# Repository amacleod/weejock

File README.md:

weejock
=======

Wee Jock is a 4x5 wireless keypad with smaller than normal key
spacing.  The name "Wee Jock" is a reference to Terry Pratchett's
[The Wee Free Men][weefreemen], and is meant to convey that this
keypad is more closely spaced than normal MX spacing.

The current design places the switches in a 17mm square grid, meaning
that only small square keycaps will work. ChosFox's [ChocFox][chocfox]
line of keycaps are approximately 16.5mm square, so they ought to work
fine. MBK keycaps are rectangular and will likely interfere with each
other horizontally.

Bill of Materials
-----------------

In addition to the Gerber file in [WeeJock-0-0-3-GERBER.zip](gerber/WeeJock-0-0-3-GERBER.zip), you will need:
 - 1 Seeed Studio XIAO BLE - [XIAO BLE nRF52840][xiaoble]
   - headers -OR- sockets and pins -OR- solder paste (see below)
 - 1 power switch - [PCM12][pcm12], [CUS-12TB][cus12tb], or equivalent
 - 1 reset button - [B3U-1000P][b3u1000p] or equivalent
 - 1 through-hole, right angle JST-PH-2 jack - [S2B-PH-K-S][s2bphks]
 - 1 3.7V LiPoly battery with a JST connector
 - 20 Kailh Choc v1 key switches (PG1350)
 - 20 diodes with a SOD123 footprint - [1N4148W][diode1n4148w] or equivalent
 - 20 keycaps no larger than 16.5mm by 16.5mm (for example, ChocFox CFX)

In principle, the power switch and JST connector are optional, but
highly recommended for battery operation. If you intend to always use
the keypad connected by USB, you could omit the battery entirely.

> [!WARNING]
> **Polarity Check**: Wee Jock revisions 1, 2, and 3 have the JST-PH
> jack connected to match "Adafruit-style" battery connectors: the
> positive (red) wire should be on the left when viewed from above.
>
> Not all batteries' connectors have the same polarity, so check
> carefully before plugging one in!

If you are hand-soldering, you will need headers for the controller,
as well as pogo pins for the RST and BAT+ pins.
 - 2 seven-pin headers - [PH1-07-UA][ph107ua] (or you can cut longer headers down to size)
   - alternatively you can use sockets such as the [Preci-Dip 310][sockets] series
   - and straight pins such as [Mill-Max 3320][straightpins]
 - 2 spring pins of a height to match the headers - [Mill-Max 0906][pogo0906]

If you intend to surface mount the controller, you will need a way to
handle the RST and BAT+ pads on the back, such as solder paste and a
rework station (or at least a hotplate).

TODO:
 - find a nice way to print a 2D color render of the PCB for inclusion in this README

[weefreemen]: https://en.wikipedia.org/wiki/The_Wee_Free_Men "The Wee Free Men"
[chocfox]: https://chosfox.com/collections/low-profile-keycaps/products/chocfox-bow?variant=43632218767554
[xiaoble]: https://www.seeedstudio.com/Seeed-XIAO-BLE-nRF52840-p-5201.html
[pcm12]: https://www.digikey.com/en/products/detail/c-k/PCM12SMTR/1640112
[cus12tb]: https://www.digikey.com/en/products/detail/nidec-components-corporation/CUS-12TB/1124222
[b3u1000p]: https://www.digikey.com/en/products/detail/omron-electronics-inc-emc-div/B3U-1000P/1534338
[s2bphks]: https://www.digikey.com/en/products/detail/jst-sales-america-inc./S2B-PH-K-S/926626
[diode1n4148w]: https://www.digikey.com/en/products/detail/smc-diode-solutions/1N4148W/6022450
[ph107ua]: https://www.digikey.com/en/products/detail/adam-tech/PH1-07-UA/9830505
[sockets]: https://www.digikey.com/en/products/detail/preci-dip/310-87-115-41-001101/3757353
[straightpins]: https://www.digikey.com/en/products/detail/mill-max-manufacturing-corp/3320-0-00-15-00-00-03-0/4147392
[pogo0906]: https://www.digikey.com/en/products/detail/mill-max-manufacturing-corp/0906-2-15-20-75-14-11-0/1147050

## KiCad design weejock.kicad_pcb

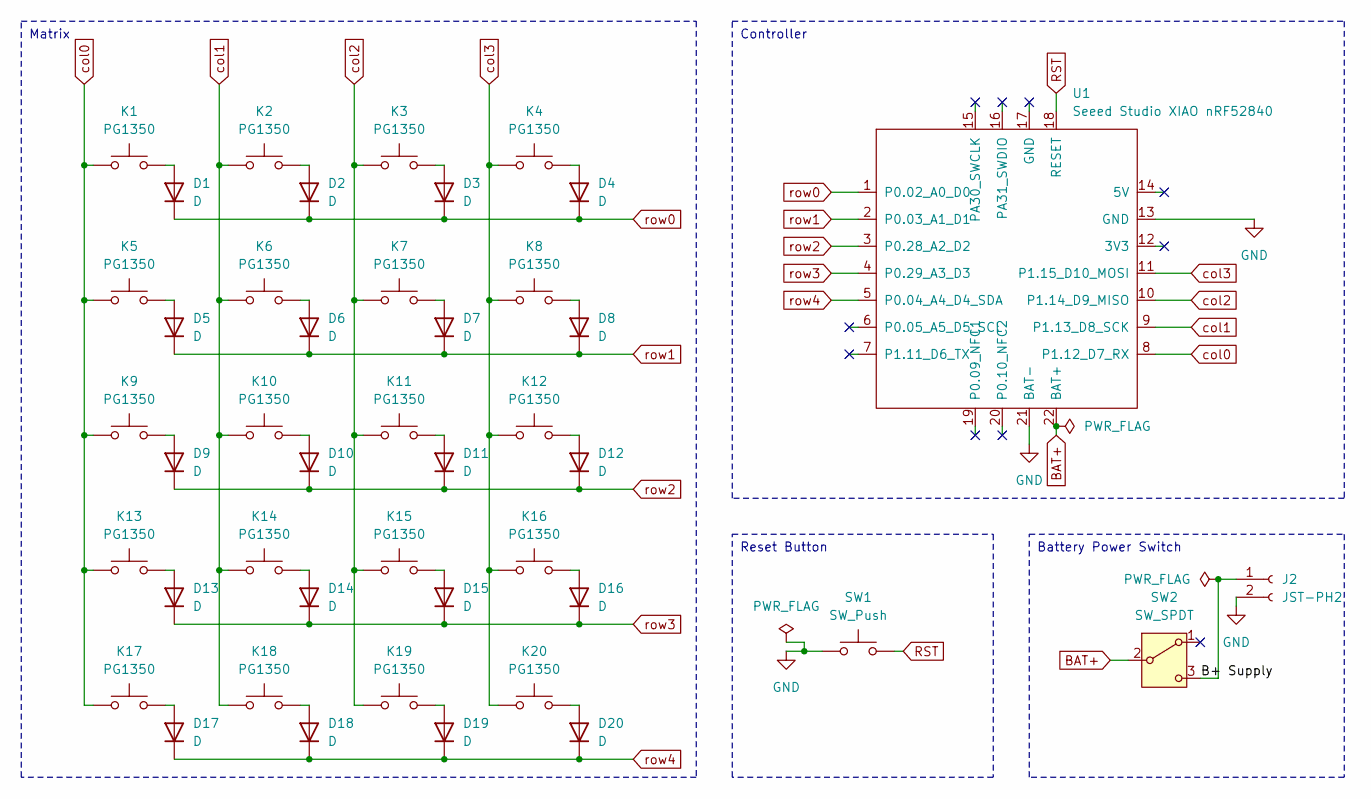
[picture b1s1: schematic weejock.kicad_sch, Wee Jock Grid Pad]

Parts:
D1, D2, D3, D4, D5, D6, D7, D8, D9, D10, D11, D12, D13, D14, D15, D16, D17, D18, D19, D20: D; D_SOD-123
J2: JST-PH2; JST_PH_S2B-PH-K_1x02_P2.00mm_Horizontal
K1, K2, K3, K4, K5, K6, K7, K8, K9, K10, K11, K12, K13, K14, K15, K16, K17, K18, K19, K20: PG1350; SW_Kailh_Choc_V1
SW1: SW_Push; SW_SPST_B3U-1000P
SW2: SW_SPDT; SW_SPDT_PCM12
U1: Seeed Studio XIAO nRF52840; Castellated XIAO with BAT+ and RST

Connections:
/B+ Supply: J2.1, SW2.3 (C)
BAT+: SW2.2 (B), U1.22 (BAT+)
GND: J2.2, SW1.1, U1.13 (GND), U1.21 (BAT-)
unnamed: D1.2 (A), K1.2
unnamed: D2.2 (A), K2.2
unnamed: D3.2 (A), K3.2
unnamed: D4.2 (A), K4.2
unnamed: D5.2 (A), K5.2
unnamed: D6.2 (A), K6.2
unnamed: D7.2 (A), K7.2
unnamed: D8.2 (A), K8.2
unnamed: D9.2 (A), K9.2
unnamed: D10.2 (A), K10.2
unnamed: D11.2 (A), K11.2
unnamed: D12.2 (A), K12.2
unnamed: D13.2 (A), K13.2
unnamed: D14.2 (A), K14.2
unnamed: D15.2 (A), K15.2
unnamed: D16.2 (A), K16.2
unnamed: D17.2 (A), K17.2
unnamed: D18.2 (A), K18.2
unnamed: D19.2 (A), K19.2
unnamed: D20.2 (A), K20.2
RST: SW1.2, U1.18 (RESET)
col0: K1.1, K5.1, K9.1, K13.1, K17.1, U1.8 (P1.12_D7_RX)
col1: K2.1, K6.1, K10.1, K14.1, K18.1, U1.9 (P1.13_D8_SCK)
col2: K3.1, K7.1, K11.1, K15.1, K19.1, U1.10 (P1.14_D9_MISO)
col3: K4.1, K8.1, K12.1, K16.1, K20.1, U1.11 (P1.15_D10_MOSI)
row0: D1.1 (K), D2.1 (K), D3.1 (K), D4.1 (K), U1.1 (P0.02_A0_D0)
row1: D5.1 (K), D6.1 (K), D7.1 (K), D8.1 (K), U1.2 (P0.03_A1_D1)
row2: D9.1 (K), D10.1 (K), D11.1 (K), D12.1 (K), U1.3 (P0.28_A2_D2)
row3: D13.1 (K), D14.1 (K), D15.1 (K), D16.1 (K), U1.4 (P0.29_A3_D3)
row4: D17.1 (K), D18.1 (K), D19.1 (K), D20.1 (K), U1.5 (P0.04_A4_D4_SDA)

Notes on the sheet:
Reset Button
Matrix
Controller
Battery Power Switch

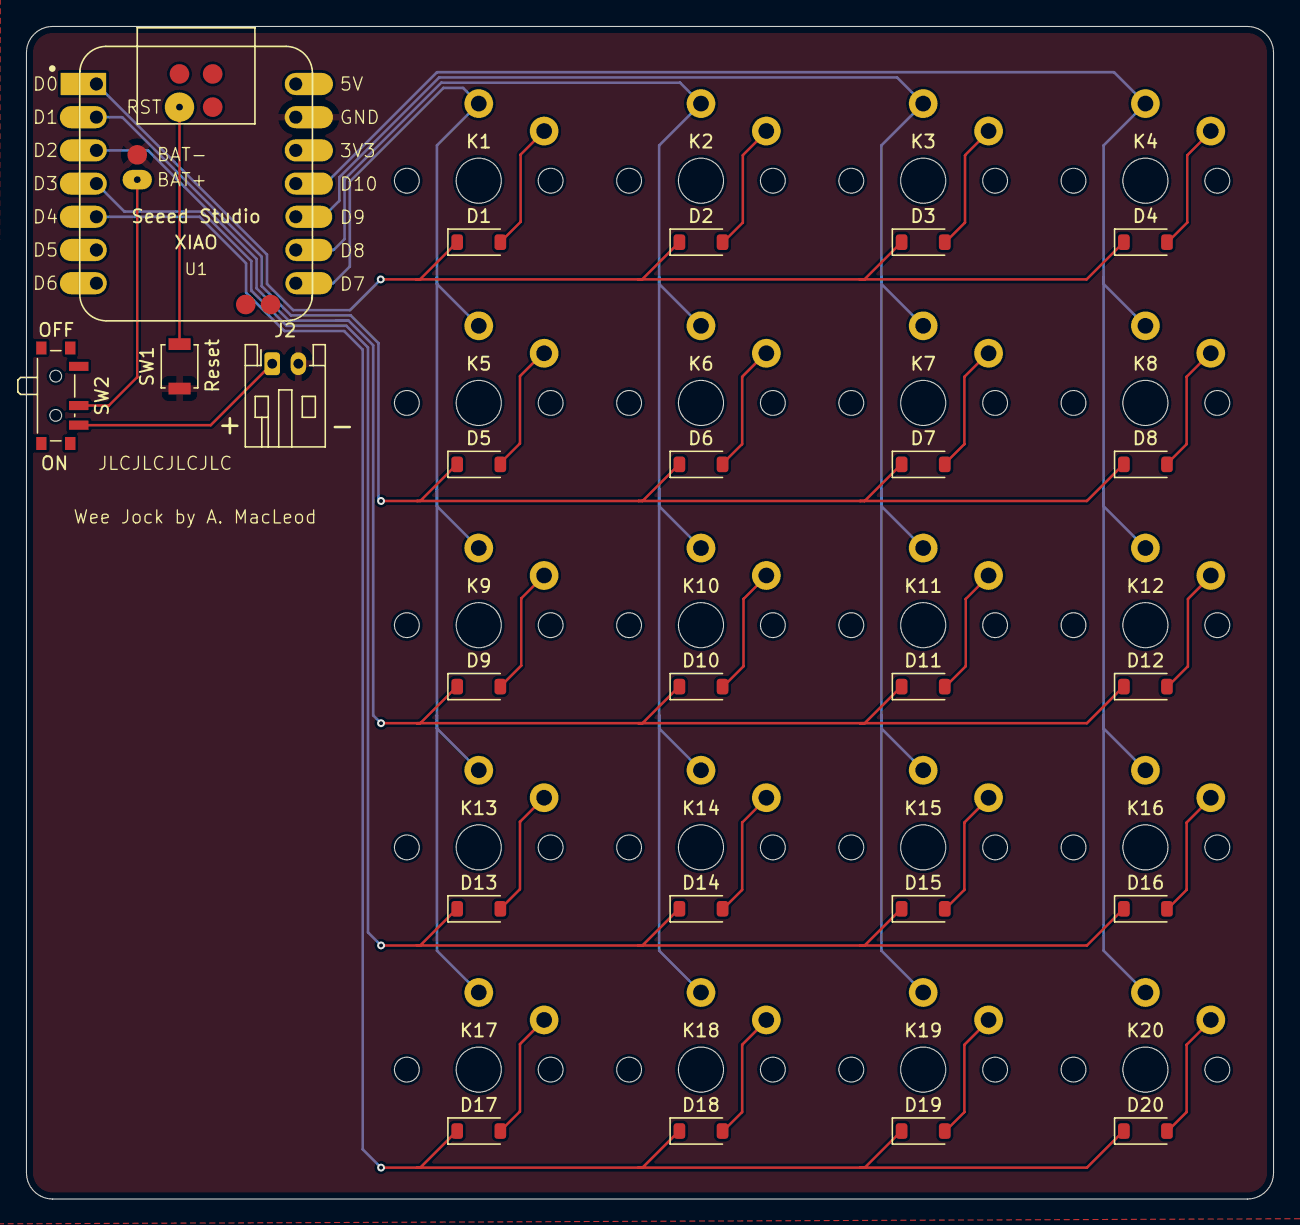
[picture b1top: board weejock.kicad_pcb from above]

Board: 2 copper layers, 95.4 x 89.7 mm, 44 parts (0 on the bottom side), 33 nets.

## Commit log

2024-10-06 Initial commit for Wee Jock grid pad
2024-10-06 Plot of schematic v0.0.1
2024-10-06 Attempting to include schematic in README
2024-10-06 Let us try the schematic with SVG instead of PNG.
2024-10-06 Missed an exclamation point.
2024-10-06 Trying PDF again.
2024-10-06 Adding title text to the image link.
2024-10-06 Back to SVG once again, but with an exclamation point this time!
2024-10-06 Adding Wee Free Men reference link.
2024-10-06 Beginning to assign footprints.
2024-10-06 Moving footprints around on the PCB layout.
2024-10-07 Routing traces.
2024-10-07 Rerouting stuff to not be too near the edge of the board.
2024-10-07 Perhaps misguided attempt to make hand-soldering holes for surface mount back pads.
2024-10-07 Fixing up footprints for better routing and access around XIAO.
2024-10-07 Forgot to check in new footprint for Seeed XIAO.
2024-10-07 Putting some TODOs in the README
2024-10-07 After-effects of a Gerber plot.
2024-10-11 Version 0.0.2 - use footprint that is both SMT and through hole friendly, and fix JST footprint.
2024-10-11 Gerber ZIP for Wee Jock v0.0.2
2024-10-11 Adding BOM to README
2024-10-11 Deleting completed or obsolete TODOs
2024-10-11 Minor changes, I think due to moving some text.
2024-10-17 Correcting XIAO BLE footprint to reverse accidental mirroring of pads.
2024-10-17 Neatening power switch and adding ON/OFF labels.
2024-10-17 Labeling reset button.
2024-10-17 Moving JST jack for better keycap clearance, and adding +/- labels.
2024-10-17 Messing with labels.
2024-10-17 Rev 3: Fix up pad placement and silkscreen labels, as well as repositioning components a little. (#5)
    * Correcting XIAO BLE footprint to reverse accidental mirroring of pads.
    * Neatening power switch and adding ON/OFF labels.
    * Labeling reset button.
    * Moving JST jack for better keycap clearance, and adding +/- labels.
    * Messing with labels.
    * Update sheet metadata to reflect version number 0.0.3
2024-10-17 Gerber ZIP for Wee Jock v0.0.3
2024-10-17 Pin labels for XIAO
2024-10-17 Update 0-0-3 Gerbers in place to include controller pin labels.
2024-10-17 More XIAO labels.
2024-10-17 Yet another in-place Gerber replacement for labels.
2024-10-18 Polarity warning.
2025-12-27 Adding build photo to the README.
2025-12-27 Adding KiBot render stuff, experimentally.
2025-12-27 Correcting which KiCad files are to be processed by KiBot
2025-12-27 Revert "Adding KiBot render stuff, experimentally."
    This reverts commit 6b6248aa328e1018a5ea4d21a5762a891cf8da32.
